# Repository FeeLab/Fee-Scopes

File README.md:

# Getting Started

Welcome to the repository on all things related to the Featherscope and Kiloscope, two light-weight head-mounted microscopes developed in the Fee lab at MIT. Our intent with this repository is to give you all the information you need to build your own scopes to use in your lab. We are also excited about people developing their own upgrades or even using elements of this project for their own microscope designs. Please let us know if you have any feedback or suggestions for improving these resources--we are always looking for ways to make this project more useful to the community!

The microscopes described in this repository are featured in [this bioRxiv paper](https://www.biorxiv.org/content/10.1101/2021.09.03.458947v2). All the analysis code in the paper can be found at [this repository](https://github.com/FeeLab/Microscope-Paper-Code), and the raw data from the paper is posted [here](https://academictorrents.com/details/aa2a3d2f5ff0b3974871db47db57bc3dabf3c192).

A fully functional system is comprised of the microscope itself, a DAQ and acquisition computer, a laser and associated illumination optics, and (optionally) a commutator for long-term recording. The components necessary for each of these subsystems are listed in `main_bom.ods` along with a cost breakdown.

# Microscope

Each microscope is built from small optical components mounted inside 3D printed parts. The optics needed for each microscope can be found under the Kiloscope and Featherscope tabs of `main_bom.ods`. The STEP files for the printed parts are located in the `body_components` folder. Technical details about the construction process can be found in the Methods section of the paper.

## Aspheric Lenses

The aspheric lens assemblies used in the Kiloscope are taken from replacement rear camera modules for the Samsung Galaxy S9 phone. These modules can be purchased online from 3rd party vendors, however the lenses then need to be carefully removed from the assembled housing. Instructions for removing the lenses from the modules can be found in `assembly_instructions`. The process should take about 20 minutes for an experienced assembler. Note that the lens material is very easy to scratch and difficult to clean, so be careful not to touch the lens faces during this process! When you have extracted the lens, you can store it safely in a PDMS device carrier (we reuse the containers that Edmund Optics ships their prisms in).

## Ground GRIN Lenses

The tube lens used in the Featherscope is a GRIN lens purchased from Edmund Optics that has been ground down to a total length of 1 mm. Ideally we would have GRINTech, the manufacturer of the original lenses, make us custom lenses with the correct length to begin with. However, GRINTech and Inscopix have signed an anticompetitive exclusive distribution agreement for one-photon calcium imaging, so we have to be a little more creative about how we get these components. We purchase lenses from Edmund Optics (part number in BOM) and have them ground down to 1.00 mm by Pioneer Precision Optics, a custom optics company based in Massachusetts.

## Fiber Bundles

The fiber bundle used in the Featherscope is made by [Acrolite](https://www.acrolite.net/products/micro-fiber-optics), a company based in New York that specializes in making impressively tiny and intricate optical fiber bundles with custom potted termination geometries. They have a great engineering department and will work with you on custom solutions if you want to design a different illumination path.

## 3D Prints

We have had success ordering prints from [Rosenberg Industries](https://www.rosenbergindustries.com), a company based in Minnesota that specializes in prints for neuroscience implant devices. Parts are printed in Formlabs Grey resin at 25 micron resolution.

## Printed Circuit Boards

We order our image sensor boards from [Speedy Circuits](http://www.speedy-circuits.com.tw/), a board house in Taiwan that specializes in small run fabrication and assembly. We highly recommend the additional cost of board assembly unless you really want to practice your BGA soldering skills! Boards can be ordered using the gerber files found in the `python_pcb` folder.

Here are the specifications for the boards if you want to order them from another board house.

| Parameter       | Value       |
| -----------     | ----------- |
| Layer Count     | 6           |
| Copper Weight   | 1.1 mil external, 0.7 mil internal |
| Board Thickness | 500 micron |
| Dimensions | 8.2 x 14.0 mm |
| Number of Holes | 146 |
| Min Hole Size | 3 mil |
| Blind Vias | L1-L4 |
| Min Trace/Space | 3 mil |
| Vias in Pad | Epoxy Filled and Plated |
| Surface Finish | Immersion gold, 2 micron |

The board design files are free to view with Altium but require an Altium license to edit. If you are a student, you can obtain an [educational license](https://www.altium.com/education/student-licenses) for free. Let us know if you would like to convert the design files to an open-source format like KiCad and we would be happy to assist.

## Assembly

Step-by-step instructions for assembling the microscopes are provided in `assembly_instructions`. Most components are secured using UV cure optical cement that can be purchased from [Edmund Optics](https://www.edmundoptics.com/f/norland-optical-adhesives/11818/) or a similar supplier. These instructions are a work in progress, so please don't hesistate to contact us if any of the steps are unclear!

## Programming

Firmware for the Attiny on the PCB can be found in `attiny_firmware`. Source code is included, with the exception of a section of `sensor_power_sequencing.c` that is restricted under NDA with Arrow, a distributor of ONSemi components. If you want access to the register settings contained in this section of the source code, contact an ONSemi distributor and request an NDA for the Python 480 programming notes.

The compiled code is contained in `Mscp_code/Release/Mscp_code.elf` and can be uploaded to the microcontroller using [Atmel Studio](https://microchipdeveloper.com/install:atstudio). We use [this programmer](https://www.microchip.com/en-us/development-tool/ATATMEL-ICE) but anything compatible with UPDI should work.

# DAQ System

## Hardware
The DAQ hardware is based on that of the [UCLA Miniscope](https://github.com/Aharoni-Lab/Miniscope-v4/wiki/DAQ-Hardware) and uses similar fabrication parameters. We had ours fabricated and assembled by [Seeed Studio](https://www.seeedstudio.com/) since these boards don't have as demanding specifications as the image sensor boards. Fabrication files can be found in the `DAQ` folder.

You will need to flash the firmware onto EEPROM before using the boards. Compile the DAQ firmware code in `cypress_firmware` using the [Cypress USB Suite](https://www.infineon.com/cms/en/design-support/tools/sdk/usb-controllers-sdk/ez-usb-fx3-software-development-kit/?utm_source=cypress&utm_medium=referral&utm_campaign=202110_globe_en_all_integration-software) and load it onto the board following the directions for the [UCLA Miniscope](https://github.com/Aharoni-Lab/Miniscope-DAQ-Cypress-firmware).

## Recording Software
The DAQ board presents itself to your computer as a webcam device, and for testing can be opened as a streaming device in [VLC](https://www.videolan.org/vlc/). For experiments, we acquire data from the microscope using [Bonsai](https://bonsai-rx.org/), a reactive programming languange designed for the multiple asynchronous data streams typical of behavioral neuroscience experiments. Bonsai has modules for recording from the UCLA Miniscope, Neuropixels, National Instruments devices, Arduinos, and various other data streams. We have written a module for our microscopes that can be downloaded from the Bonsai package manager. The module outputs video data in RGB565 format and allows for control of the image sensor gain. The source code can be found in `bonsai_module`.

An example Bonsai script for recording can also be found in `bonsai_module`. This script saves video from both the microscope and from an animal tracking camera simultaneously, while recording timestamps for each frame of both streams. Video is saved in the raw RGB565 format, but the script also performs realtime conversion to a human-interpretable grayscale image for online monitoring of the fluorescence signal.

# Illumination Optics

## Laser
Illumination light is provided by a multimode 473 nm laser similar to those used in optogenetics experiments. We use the MBL-473-50mW laser from [CNI Laser](http://www.cnilaser.com/), an optics company based in China with a wide range of turnkey optical systems for neuroscience applications. If you are planning on imaging at a different wavelength or have other specific requirements, they will probably be able to match your requirements.

## Coupling Optics
Light from the laser is coupled into the fiber using a system of optics detailed in the methods section of the paper and in `main_bom.ods`. Optics are assembled in a Thorlabs cage plate system for ease of alignment.

In the paper, we include a shutter so that illumination can be turned off when not recording to avoid photobleaching. However, the MBL-473-50mW laser from CNI has a TTL modulation input that can also be used to turn the laser on and off. The shutter is only needed in settings where the illumination power needs to be very stable over the course of the recording, as modulating the laser current results in temporary thermal instability in the laser cavity and a period of minor intensity variability.

The despeckler used in the paper has been discontinued since publication. Luckily, we have since developed a homemade despeckler that is both cheaper and more efficient than the previous despeckler, and can be built by hand in a few hours. We will post construction details as soon as we have the release version finalized, so follow this space for more details.

# Commutator
For recording sessions that last 30 minutes or less, you may be able to use a static recording setup without the animal twisting the tether excessively. However, for longer-term recordings or with very active or sensitive animals (e.g. birds), a commutator will be necessary to avoid tether wrapping issues. 

We have designed an actively driven commutator for the microscopes that simultaneously transmits power, data, and illumination light. Design files, along with notes on assembly, can be found in the `commutator` directory as well as in `main_bom.ods`.

## Machined components
The commutator base consists of two custom machined aluminum plates. Drawings for these plates can be found in the `commutator` folder. They can be fabricated by your favorite machine shop or online machining service (we use [Protolabs](https://www.protolabs.com/services/cnc-machining/)).

## PCB
The commutator PCB provides regulated power to the microscope and sends a torque signal to the motor controller. It is a simple two-layer board and can be fabricated by [OSHPark](https://oshpark.com/). Design files can be found in `commutator/sensor_board` in EAGLE format. Autodesk offers free educational licenses for EAGLE.

## Motor Controller Box
The commutator is driven by a Faulhaber DC motor controlled by a custom motor driver. The PCB for the driver can be found in `commutator/motor_controller` and can be fabricated by OSHPark. Components and assembly notes for the driver box can also be found in `commutator/motor_controller`.

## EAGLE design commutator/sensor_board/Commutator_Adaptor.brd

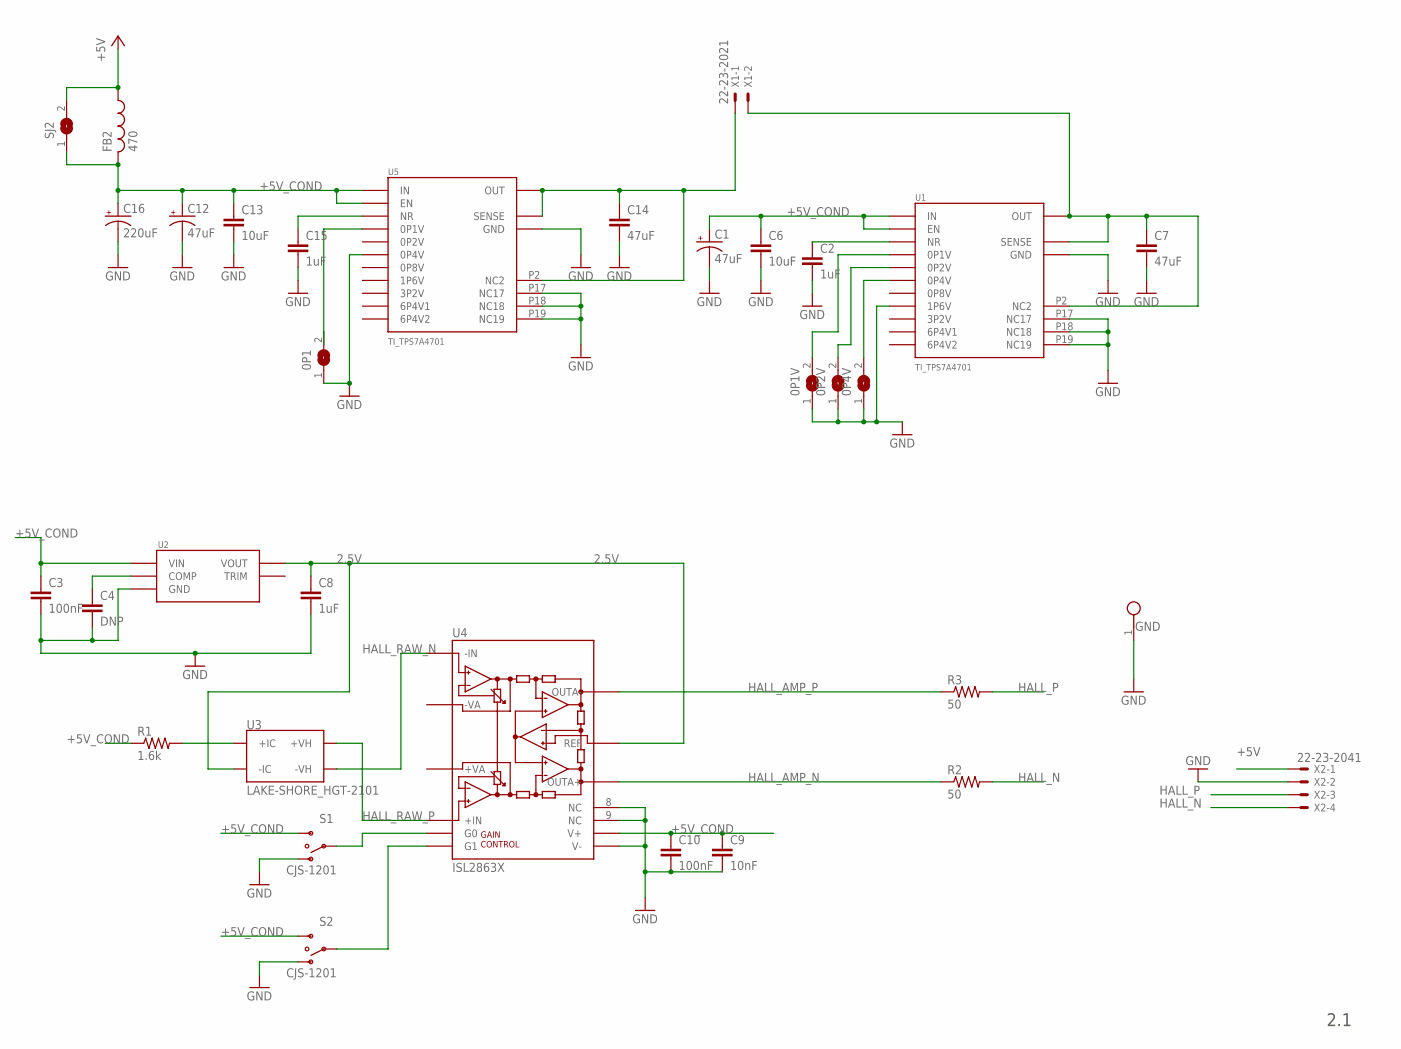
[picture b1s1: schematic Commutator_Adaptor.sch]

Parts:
0P1, 0P1V, 0P2V, 0P4V: SJ
C1, C12: 47uF; 1210POL
C2, C8, C15: 1uF; 0603
C3, C10: 100nF; 0402
C4: DNP; 0402
C6, C13: 10uF; 0805
C7, C14: 47uF; 1210
C9: 10nF; 0402
C16: 220uF; JA0
FB2: 470; 0603
GND: TESTPOINT_SMALL
R1: 1.6k; 0402
R2, R3: 50; 0402
S1, S2: CJS-1201; CJS-1201A1
SJ2: SJ
U1, U5: TI_TPS7A4701; 20-VQFN(5X5)
U2: ISL21090; SO08
U3: LAKE-SHORE_HGT-2101; HGT-2101-SIDE
U4: ISL2863X; TSSOP14
X1: 22-23-2021
X2: 22-23-2041

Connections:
1P8: C14.POS (1), U5.P1 (OUT), U5.P2 (NC2), U5.P3 (SENSE), U5.P20 (OUT), X1.1
2.5V: C8.1, U2.6 (VOUT), U3.PIN1 (-IC), U4.11 (REF)
3P3: C7.POS (1), U1.P1 (OUT), U1.P2 (NC2), U1.P3 (SENSE), U1.P20 (OUT), X1.2
+5V: FB2.1, SJ2.2, X2.1
+5V_COND: C1.POS (+), C3.1, C6.1, C9.1, C10.1, C12.POS (+), C13.1, C16.POS (+), FB2.2, R1.1, S1.P$3 (S), S2.P$3 (S), SJ2.1, U1.P13 (EN), U1.P15 (IN), U1.P16 (IN), U2.2 (VIN), U4.14 (V+), U5.P13 (EN), U5.P15 (IN), U5.P16 (IN)
GND: 0P1.1, 0P1V.1, 0P2V.1, 0P4V.1, C1.NEG (-), C2.2, C3.2, C4.2, C6.2, C7.NEG (2), C8.2, C9.2, C10.2, C12.NEG (-), C13.2, C14.NEG (2), C15.2, C16.NEG (-), GND.1, S1.P$1 (O), S2.P$1 (O), U1.P7 (GND), U1.P8 (1P6V), U1.P17 (NC17), U1.P18 (NC18), U1.P19 (NC19), U1.THERMAL@1 (GND), U1.THERMAL@2 (GND), U1.THERMAL@3 (GND), U1.THERMAL@4 (GND), U1.THERMAL@5 (GND), U1.THERMAL@6 (GND), U1.THERMAL@7 (GND), U1.THERMAL@8 (GND), U1.THERMAL@9 (GND), U1.THERMAL@10 (GND), U2.4 (GND), U4.7 (V-), U4.8 (NC), U4.9 (NC), U5.P7 (GND), U5.P10 (0P4V), U5.P17 (NC17), U5.P18 (NC18), U5.P19 (NC19), U5.THERMAL@1 (GND), U5.THERMAL@2 (GND), U5.THERMAL@3 (GND), U5.THERMAL@4 (GND), U5.THERMAL@5 (GND), U5.THERMAL@6 (GND), U5.THERMAL@7 (GND), U5.THERMAL@8 (GND), U5.THERMAL@9 (GND), U5.THERMAL@10 (GND), X2.2
HALL_AMP_N: R2.1, U4.12 (OUTA+)
HALL_AMP_P: R3.1, U4.10 (OUTA-)
HALL_N: R2.2, X2.4
HALL_P: R3.2, X2.3
HALL_RAW_N: U3.WIRE1 (-VH), U4.5 (-IN)
HALL_RAW_P: U3.PIN2 (+VH), U4.4 (+IN)
I_HALL: R1.2, U3.WIRE2 (+IC)
unnamed: C4.1, U2.3 (COMP)
unnamed: S1.P$2, U4.1 (G0)
unnamed: C15.1, U5.P14 (NR)
unnamed: S2.P$2, U4.2 (G1)
unnamed: 0P4V.2, U1.P10 (0P4V)
unnamed: C2.1, U1.P14 (NR)
unnamed: 0P2V.2, U1.P11 (0P2V)
unnamed: 0P1.2, U5.P12 (0P1V)
unnamed: 0P1V.2, U1.P12 (0P1V)

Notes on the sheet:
2.1

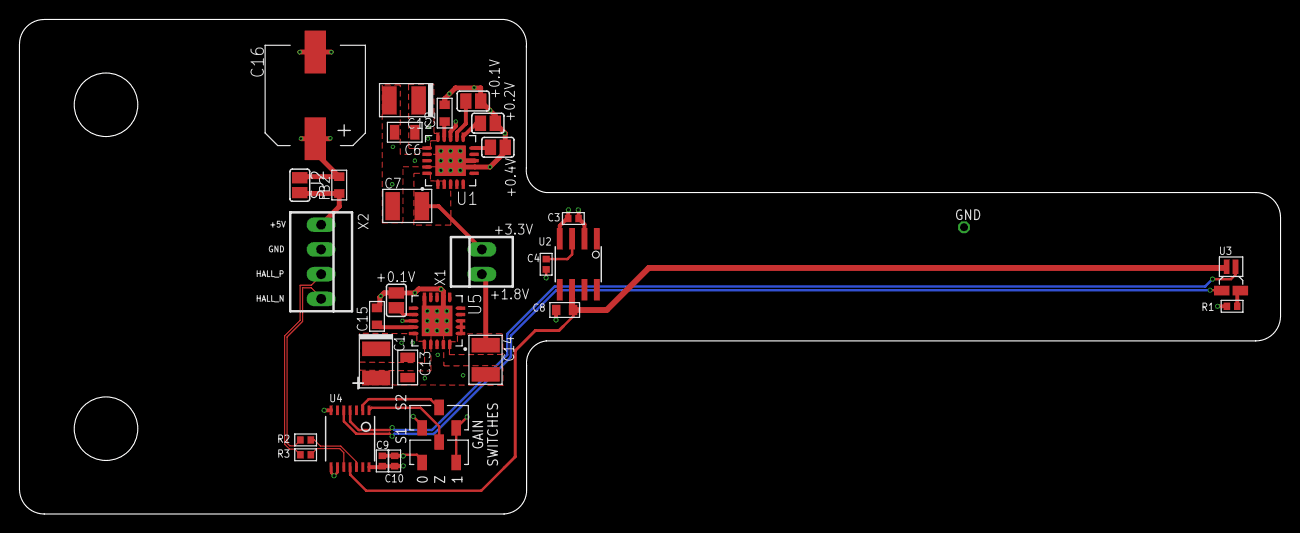
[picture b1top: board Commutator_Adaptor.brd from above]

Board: 4 copper layers, 129.5 x 50.8 mm, 33 parts (0 on the bottom side), 22 nets.

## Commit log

2021-09-08 added DAQ files
2021-09-08 added commutator board
2021-09-09 added body component files
2021-10-21 added pcb files
2022-05-12 revised python pcb for speedy circuits, updated BOM
2022-05-12 updated BOM, added gerbers for rev 1.1
2022-05-17 replaced opamp on PCB
2022-05-17 added new kiloscope baseplate design
2022-05-17 added main BOM
2022-05-17 updated main BOM
2022-05-17 added scope assembly instructions
2022-05-17 added commutator 3D model
2022-05-17 added commutator build instructions
2022-05-25 updated commutator
2022-06-07 Add cypress firmware
2022-06-07 Add bonsai module
2022-08-29 added attiny firmware
2022-09-07 added pcb images
2022-09-07 updated images
2022-09-07 added images
2022-09-07 removed submodule
2022-09-08 split assembly instructions
2022-09-08 added disassembly instructions
2022-09-12 updated assembly instructions
2023-04-07 added images for assembly instructions
2024-09-11 exported assembly instructions as pdf
2025-01-30 updated kiloscope assembly instructions
